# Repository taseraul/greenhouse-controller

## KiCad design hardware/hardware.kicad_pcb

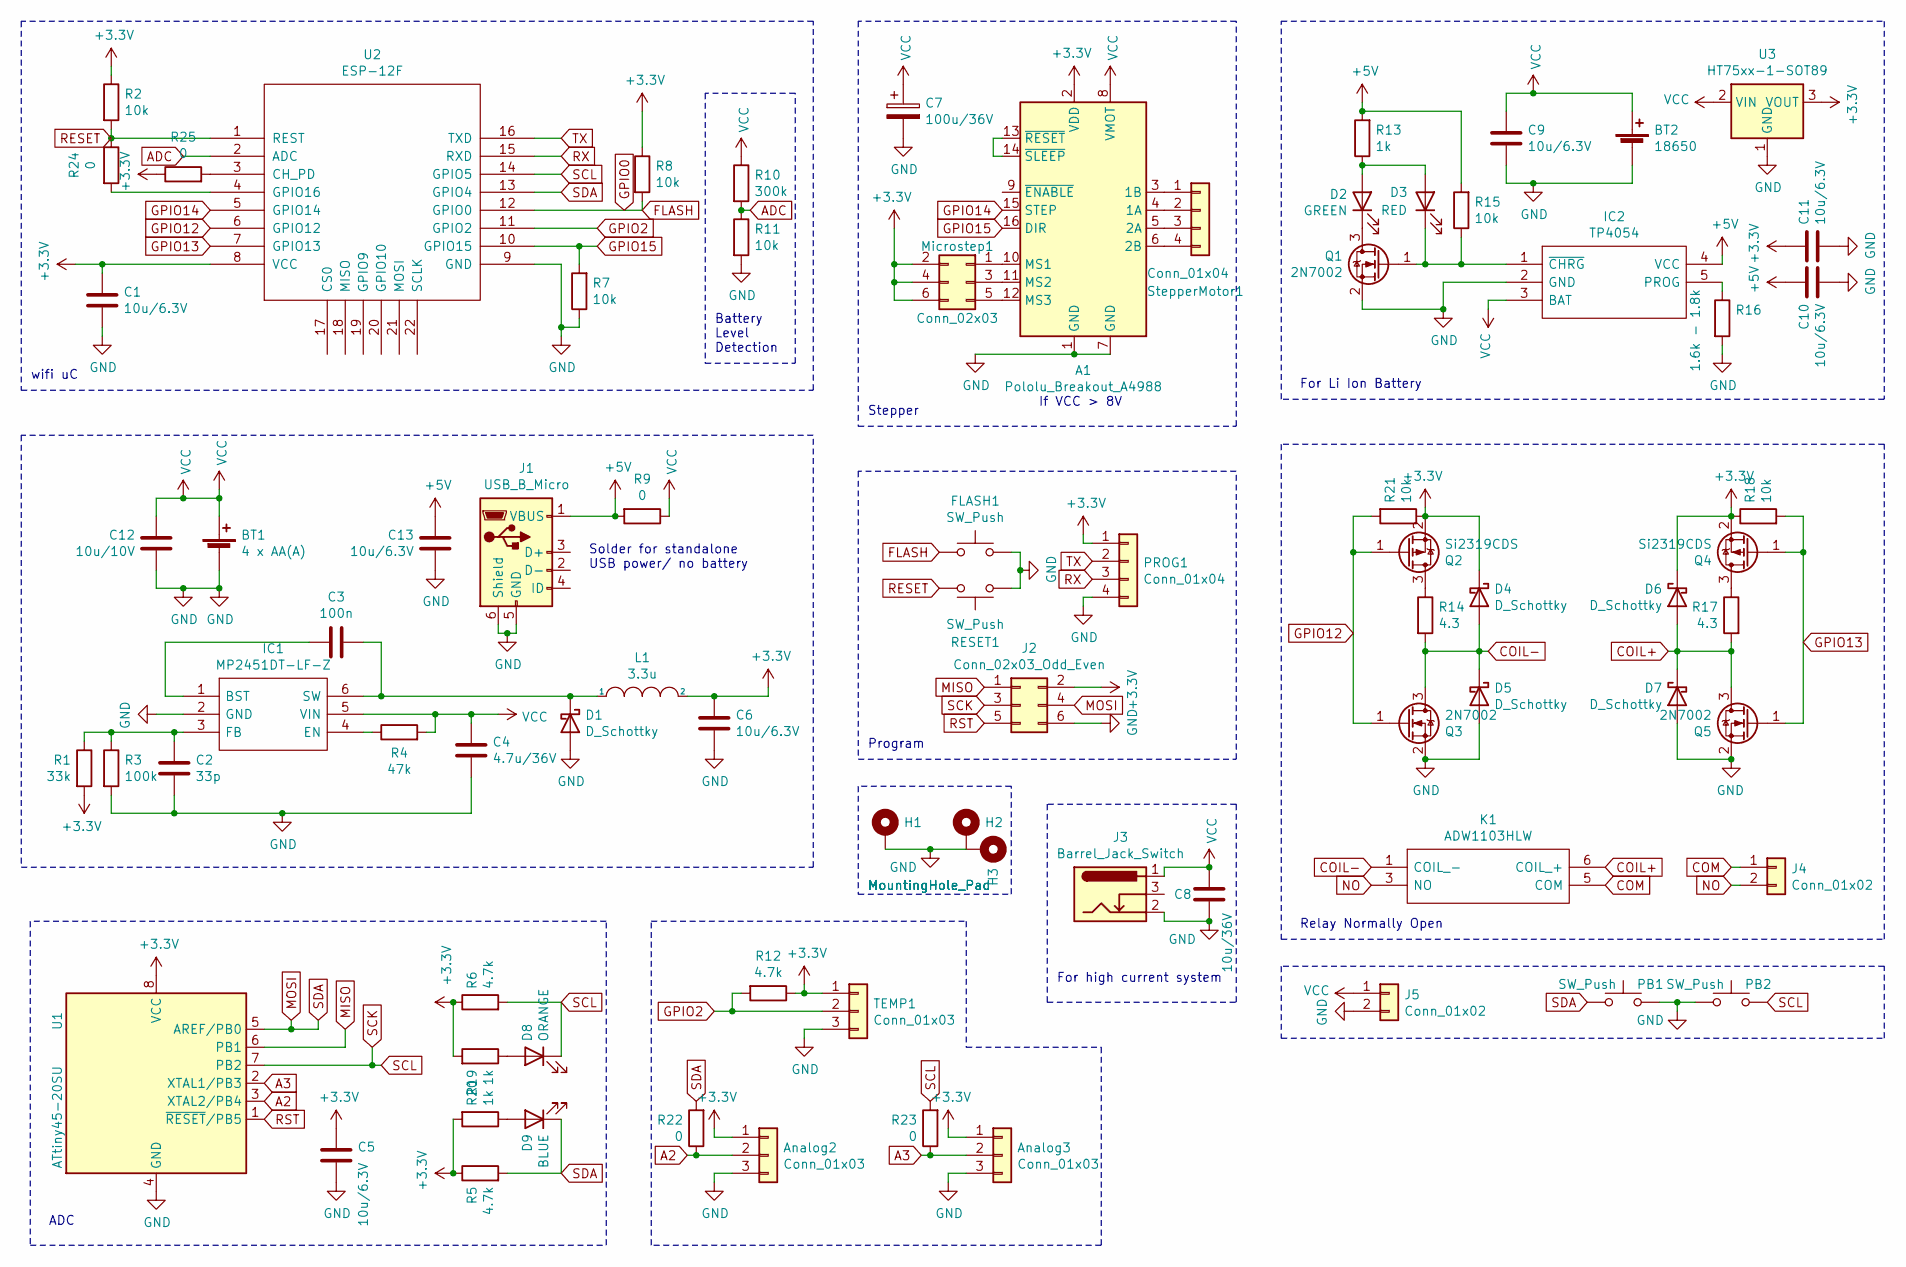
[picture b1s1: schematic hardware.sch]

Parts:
A1: Pololu_Breakout_A4988; Pololu_Breakout-16_15.2x20.3mm
Analog2, Analog3: Conn_01x03; JST_PH_S3B-PH-SM4-TB_1x03-1MP_P2.00mm_Horizontal
BT1: 4 x AA(A); PinHeader_1x02_P2.54mm_Vertical
BT2: 18650; 1043
C1, C5, C6, C9, C10, C11, C13: 10u/6.3V; C_0402_1005Metric
C2: 33p; C_0402_1005Metric
C3: 100n; C_0402_1005Metric
C4: 4.7u/36V; C_1206_3216Metric
C7: 100u/36V; CP_Elec_8x10
C8: 10u/36V; C_1206_3216Metric
C12: 10u/10V; C_0603_1608Metric
D1, D4, D5, D6, D7: D_Schottky; D_SOD-123
D2: GREEN; LED_0805_2012Metric
D3: RED; LED_0805_2012Metric
D8: ORANGE; LED_0805_2012Metric
D9: BLUE; LED_0805_2012Metric
FLASH1: SW_Push; SW_SPST_EVQP7A
H1, H2, H3: MountingHole_Pad; MountingHole_3.7mm_Pad
IC1: MP2451DT-LF-Z; SOT95P280X145-6N; Mouser Part Number 946-MP2451DTLFZ
IC2: TP4054; SOT95P280X100-5N; Manufacturer_Part_Number TP4054
J1: USB_B_Micro; USB_Micro-B_Molex-105017-0001
J2: Conn_02x03_Odd_Even; PinHeader_2x03_P2.54mm_Vertical_SMD
J3: Barrel_Jack_Switch; BarrelJack_Wuerth_6941xx301002
J4: Conn_01x02; TerminalBlock_Phoenix_MKDS-1,5-2_1x02_P5.00mm_Horizontal
J5: Conn_01x02; JST_PH_S2B-PH-SM4-TB_1x02-1MP_P2.00mm_Horizontal
K1: ADW1103HLW; Mouser Part Number 769-ADW1103HLW
L1: 3.3u; L_Bourns-SRN4018
Microstep1: Conn_02x03; PinHeader_2x03_P2.54mm_Vertical_SMD
PB1, PB2: SW_Push; SW_SPST_EVQP7A
PROG1: Conn_01x04; JST_PH_S4B-PH-SM4-TB_1x04-1MP_P2.00mm_Horizontal
Q1, Q3, Q5: 2N7002; SOT-23
Q2, Q4: Si2319CDS; SOT-23
R1: 33k; R_0402_1005Metric
R2, R7, R8, R11, R15, R18, R21: 10k; R_0402_1005Metric
R3: 100k; R_0402_1005Metric
R4: 47k; R_0402_1005Metric
R5, R6, R12: 4.7k; R_0402_1005Metric
R9, R22, R23, R24, R25: 0; R_0402_1005Metric
R10: 300k; R_0402_1005Metric
R13, R19, R20: 1k; R_0402_1005Metric
R14, R17: 4.3; R_0603_1608Metric
R16: 1.6k - 1.8k; R_0805_2012Metric
RESET1: SW_Push; SW_SPST_EVQP7A
StepperMotor1: Conn_01x04; JST_PH_S4B-PH-SM4-TB_1x04-1MP_P2.00mm_Horizontal
TEMP1: Conn_01x03; JST_PH_S3B-PH-SM4-TB_1x03-1MP_P2.00mm_Horizontal
U1: ATtiny45-20SU; SOIJ-8_5.3x5.3mm_P1.27mm
U2: ESP-12F; ESP-12E_SMD
U3: HT75xx-1-SOT89; SOT-89-3

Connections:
+3V3: A1.2 (VDD), Analog2.1, Analog3.1, C1.1, C5.1, C6.1, C11.1, D4.1 (K), D6.1 (K), J2.2, L1.2, Microstep1.2, Microstep1.4, Microstep1.6, PROG1.1, Q2.2 (S), Q4.2 (S), R1.2, R2.1, R5.1, R6.1, R8.1, R12.1, R18.1, R19.2, R20.2, R21.1, R25.1, TEMP1.1, U1.8 (VCC), U2.8 (VCC), U3.3 (VOUT)
+5V: C10.1, C13.1, IC2.4 (VCC), J1.1 (VBUS), R9.2, R13.2, R15.2
A2: Analog2.2, R22.1, U1.3 (XTAL2/PB4)
A3: Analog3.2, R23.1, U1.2 (XTAL1/PB3)
ADC: R10.2, R11.1, U2.2 (ADC)
COIL+: D6.2 (A), D7.1 (K), K1.6 (COIL_+), Q5.3 (D), R17.2
COIL-: D4.2 (A), D5.1 (K), K1.1 (COIL_-), Q3.3 (D), R14.2
COM: J4.1, K1.5 (COM)
FLASH: FLASH1.1, R8.2, U2.12 (GPIO0)
GND: A1.1 (GND), A1.7 (GND), Analog2.3, Analog3.3, BT1.2 (-), BT2.2 (-), C1.2, C2.2, C4.2, C5.2, C6.2, C7.2, C8.2, C9.2, C10.2, C11.2, C12.2, C13.2, D1.2 (A), D5.2 (A), D7.2 (A), FLASH1.2, H1.1, H2.1, H3.1, IC1.2 (GND), IC2.2 (GND), J1.5 (GND), J1.6 (Shield), J2.6, J3.2, J5.2, PB1.2, PB2.2, PROG1.4, Q1.2 (S), Q3.2 (S), Q5.2 (S), R3.2, R7.1, R11.2, R16.2, RESET1.2, TEMP1.3, U1.4 (GND), U2.9 (GND), U3.1 (GND)
GPIO2: R12.2, TEMP1.2, U2.11 (GPIO2)
GPIO12: Q2.1 (G), Q3.1 (G), R21.2, U2.6 (GPIO12)
GPIO13: Q4.1 (G), Q5.1 (G), R18.2, U2.7 (GPIO13)
GPIO14: A1.15 (STEP), U2.5 (GPIO14)
GPIO15: A1.16 (DIR), R7.2, U2.10 (GPIO15)
MISO: J2.1, U1.6 (PB1)
MOSI: D9.1 (K), J2.4, PB1.1, R5.2, R22.2, U1.5 (AREF/PB0), U2.13 (GPIO4)
NO: J4.2, K1.3 (NO)
unnamed: A1.3 (1B), StepperMotor1.1
unnamed: A1.4 (1A), StepperMotor1.2
unnamed: A1.5 (2A), StepperMotor1.3
unnamed: A1.6 (2B), StepperMotor1.4
unnamed: A1.10 (MS1), Microstep1.1
unnamed: A1.11 (MS2), Microstep1.3
unnamed: A1.12 (MS3), Microstep1.5
unnamed: A1.13 (~RESET), A1.14 (~SLEEP)
unnamed: C2.1, IC1.3 (FB), R1.1, R3.1
unnamed: C3.1, IC1.1 (BST)
unnamed: C3.2, D1.1 (K), IC1.6 (SW), L1.1
unnamed: D2.1 (K), Q1.3 (D)
unnamed: D2.2 (A), D3.2 (A), R13.1
unnamed: D3.1 (K), IC2.1 (~CHRG), Q1.1 (G), R15.1
unnamed: D8.2 (A), R19.1
unnamed: D9.2 (A), R20.1
unnamed: IC1.4 (EN), R4.1
unnamed: IC2.5 (PROG), R16.1
unnamed: Q2.3 (D), R14.1
unnamed: Q4.3 (D), R17.1
unnamed: R24.2, U2.4 (GPIO16)
unnamed: R25.2, U2.3 (CH_PD)
RESET: R2.2, R24.1, RESET1.1, U2.1 (REST)
RST: J2.5, U1.1 (~RESET~/PB5)
RX: PROG1.3, U2.15 (RXD)
SCK: D8.1 (K), J2.3, PB2.1, R6.2, R23.2, U1.7 (PB2), U2.14 (GPIO5)
TX: PROG1.2, U2.16 (TXD)
VCC: A1.8 (VMOT), BT1.1 (+), BT2.1 (+), C4.1, C7.1, C8.1, C9.1, C12.1, IC1.5 (VIN), IC2.3 (BAT), J3.1, J5.1, R4.2, R9.1, R10.1, U3.2 (VIN)

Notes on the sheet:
Solder for standalone USB power/ no battery
For high current system
For Li Ion Battery
Program
ADC
If VCC > 8V
Relay Normally Open
Stepper
wifi uC
Battery Level Detection

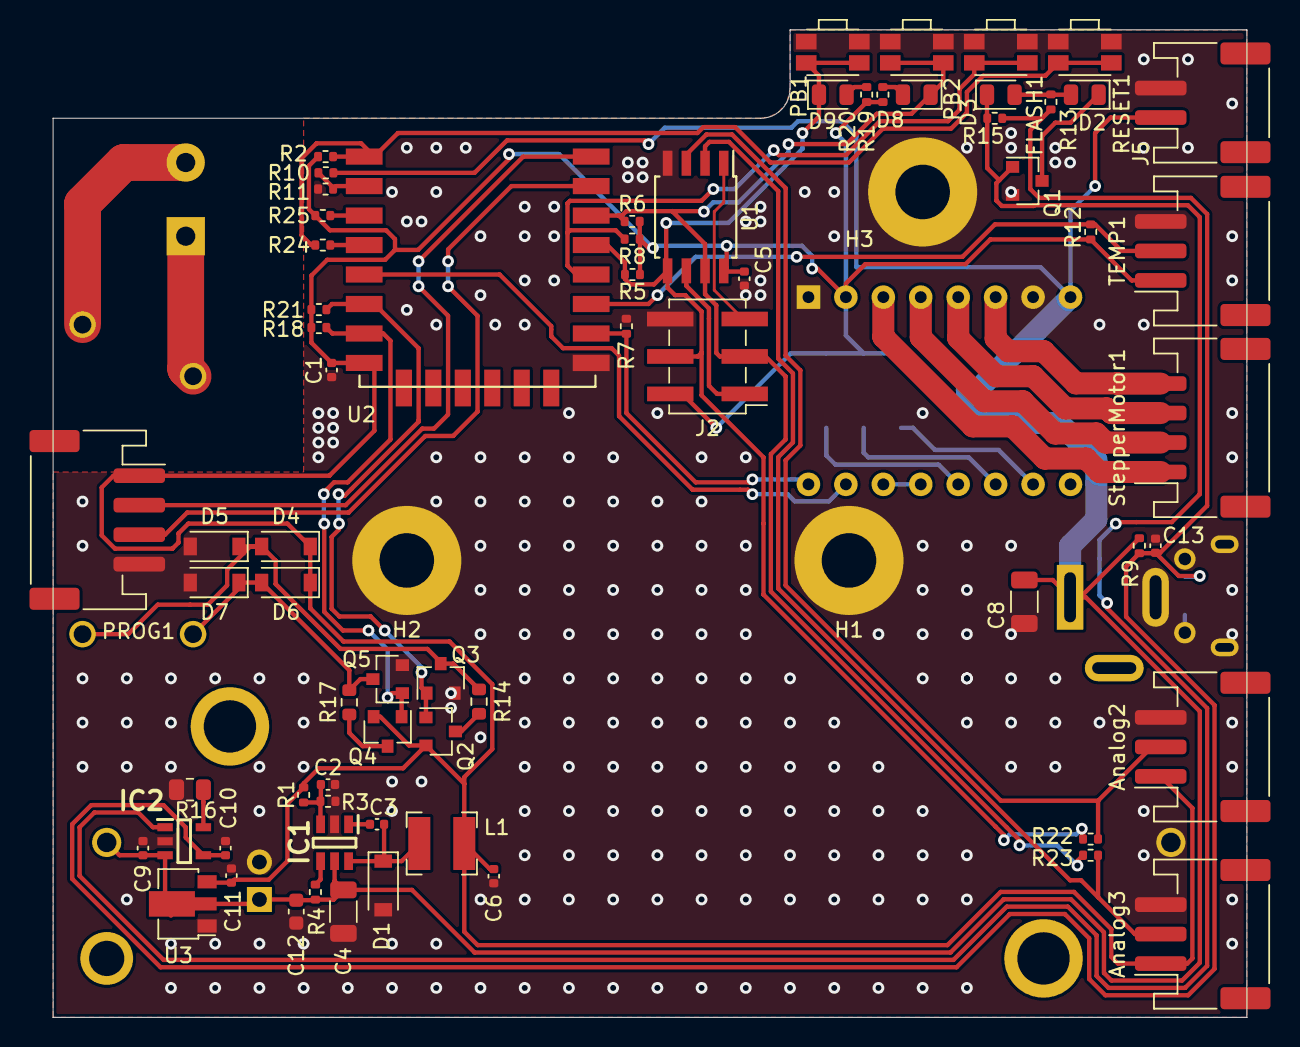
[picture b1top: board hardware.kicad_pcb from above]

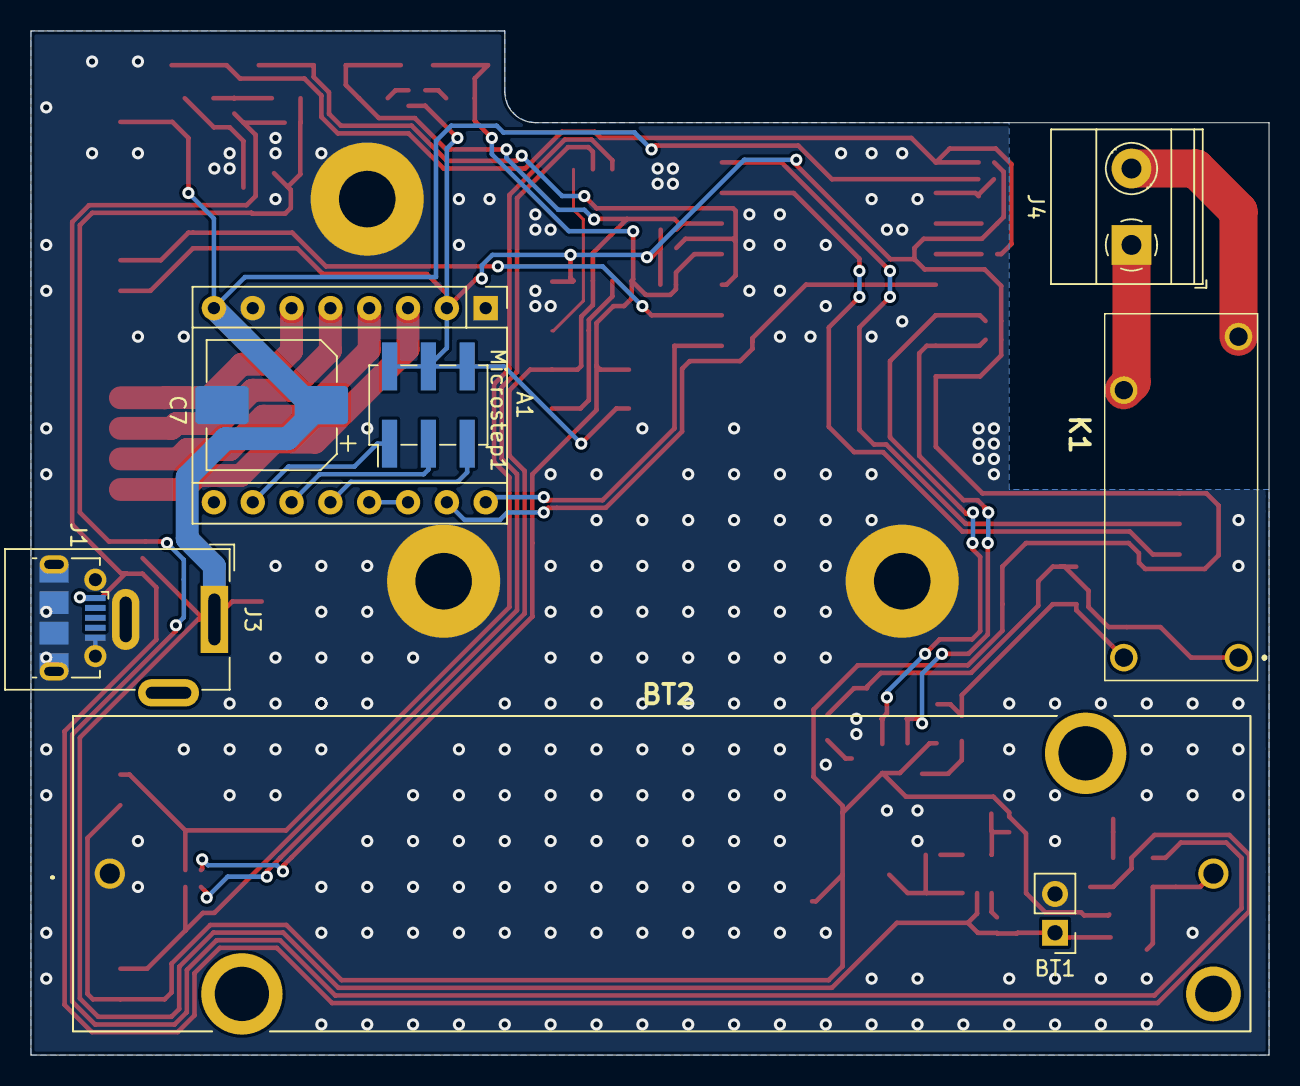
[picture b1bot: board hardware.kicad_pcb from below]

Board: 2 copper layers, 81.0 x 67.0 mm, 80 parts (9 on the bottom side), 46 nets.

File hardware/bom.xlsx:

Comment | Designator | Footprint | LCSC Part #（optional）
2N7002 | Q1,Q5,Q3 | SOT-23 | C8545
ESP-12F | U2 | ESP-12E_SMD | C82891
0 | R25,R24,R23,R22,R9 | R_0402_1005Metric | C17168
4 x AA(A) | BT1 | PinHeader_1x02_P2.54mm_Vertical
10u/6.3V | C13,C11,C10,C9,C6,C5,C1 | C_0402_1005Metric | C15525
10k | R21,R18,R15,R11,R8,R7,R2 | R_0402_1005Metric | C25744
4.3 | R14,R17 | R_0603_1608Metric
1k | R20,R19,R13 | R_0402_1005Metric | C11702
BLUE | D9 | LED_0805_2012Metric | C2293
ORANGE | D8 | LED_0805_2012Metric | C2296
18650 | BT2 | 1043
MountingHole_Pad | H3,H2,H1 | MountingHole_3.7mm_Pad
SW_Push | RESET1,PB2,PB1,FLASH1 | SW_SPST_EVQP7A
Conn_01x03 | TEMP1,Analog3,Analog2 | JST_PH_S3B-PH-SM4-TB_1x03-1MP_P2.00mm_Horizontal
Conn_01x04 | StepperMotor1,PROG1 | JST_PH_S4B-PH-SM4-TB_1x04-1MP_P2.00mm_Horizontal
Conn_01x02 | J5 | JST_PH_S2B-PH-SM4-TB_1x02-1MP_P2.00mm_Horizontal
HT75xx-1-SOT89 | U3 | SOT-89-3 | C14289
ATtiny45-20SU | U1 | SOIJ-8_5.3x5.3mm_P1.27mm | C152211
1.6k - 1.8k | R16 | R_0603_1608Metric | C17398
4.7k | R12,R6,R5 | R_0402_1005Metric | C25900
300k | R10 | R_0402_1005Metric | C25774
47k | R4 | R_0402_1005Metric | C25792
100k | R3 | R_0402_1005Metric | C25741
33k | R1 | R_0402_1005Metric | C25779
Si2319CDS | Q4,Q2 | SOT-23 | C10487
Conn_02x03 | Microstep1 | PinHeader_2x03_P2.54mm_Vertical_SMD
3.3u | L1 | L_Bourns-SRN4018 | C408336
ADW1103HLW | K1 | ADW1103HLW
Conn_01x02 | J4 | TerminalBlock_Phoenix_MKDS-1,5-2_1x02_P5.00mm_Horizontal
Barrel_Jack_Switch | J3 | BarrelJack_Wuerth_6941xx301002
Conn_02x03_Odd_Even | J2 | PinHeader_2x03_P2.54mm_Vertical_SMD
USB_B_Micro | J1 | USB_Micro-B_Molex-105017-0001
TP4054 | IC2 | SOT95P280X100-5N | C32574
MP2451DT-LF-Z | IC1 | SOT95P280X145-6N | C14123
D_Schottky | D7,D6,D5,D4,D1 | D_SOD-123 | C8598
RED | D3 | LED_0805_2012Metric | C2297
GREEN | D2 | LED_0805_2012Metric | C2296
10u/10V | C12 | C_0603_1608Metric | C19702
10u/36V | C8 | C_1206_3216Metric | C13585
100u/36V | C7 | CP_Elec_8x10
4.7u/36V | C4 | C_1206_3216Metric | C29823
100n | C3 | C_0402_1005Metric | C1525
33p | C2 | C_0402_1005Metric | C1562
Pololu_Breakout_A4988 | A1 | Pololu_Breakout-16_15.2x20.3mm

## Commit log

2021-05-06 Added hardware
